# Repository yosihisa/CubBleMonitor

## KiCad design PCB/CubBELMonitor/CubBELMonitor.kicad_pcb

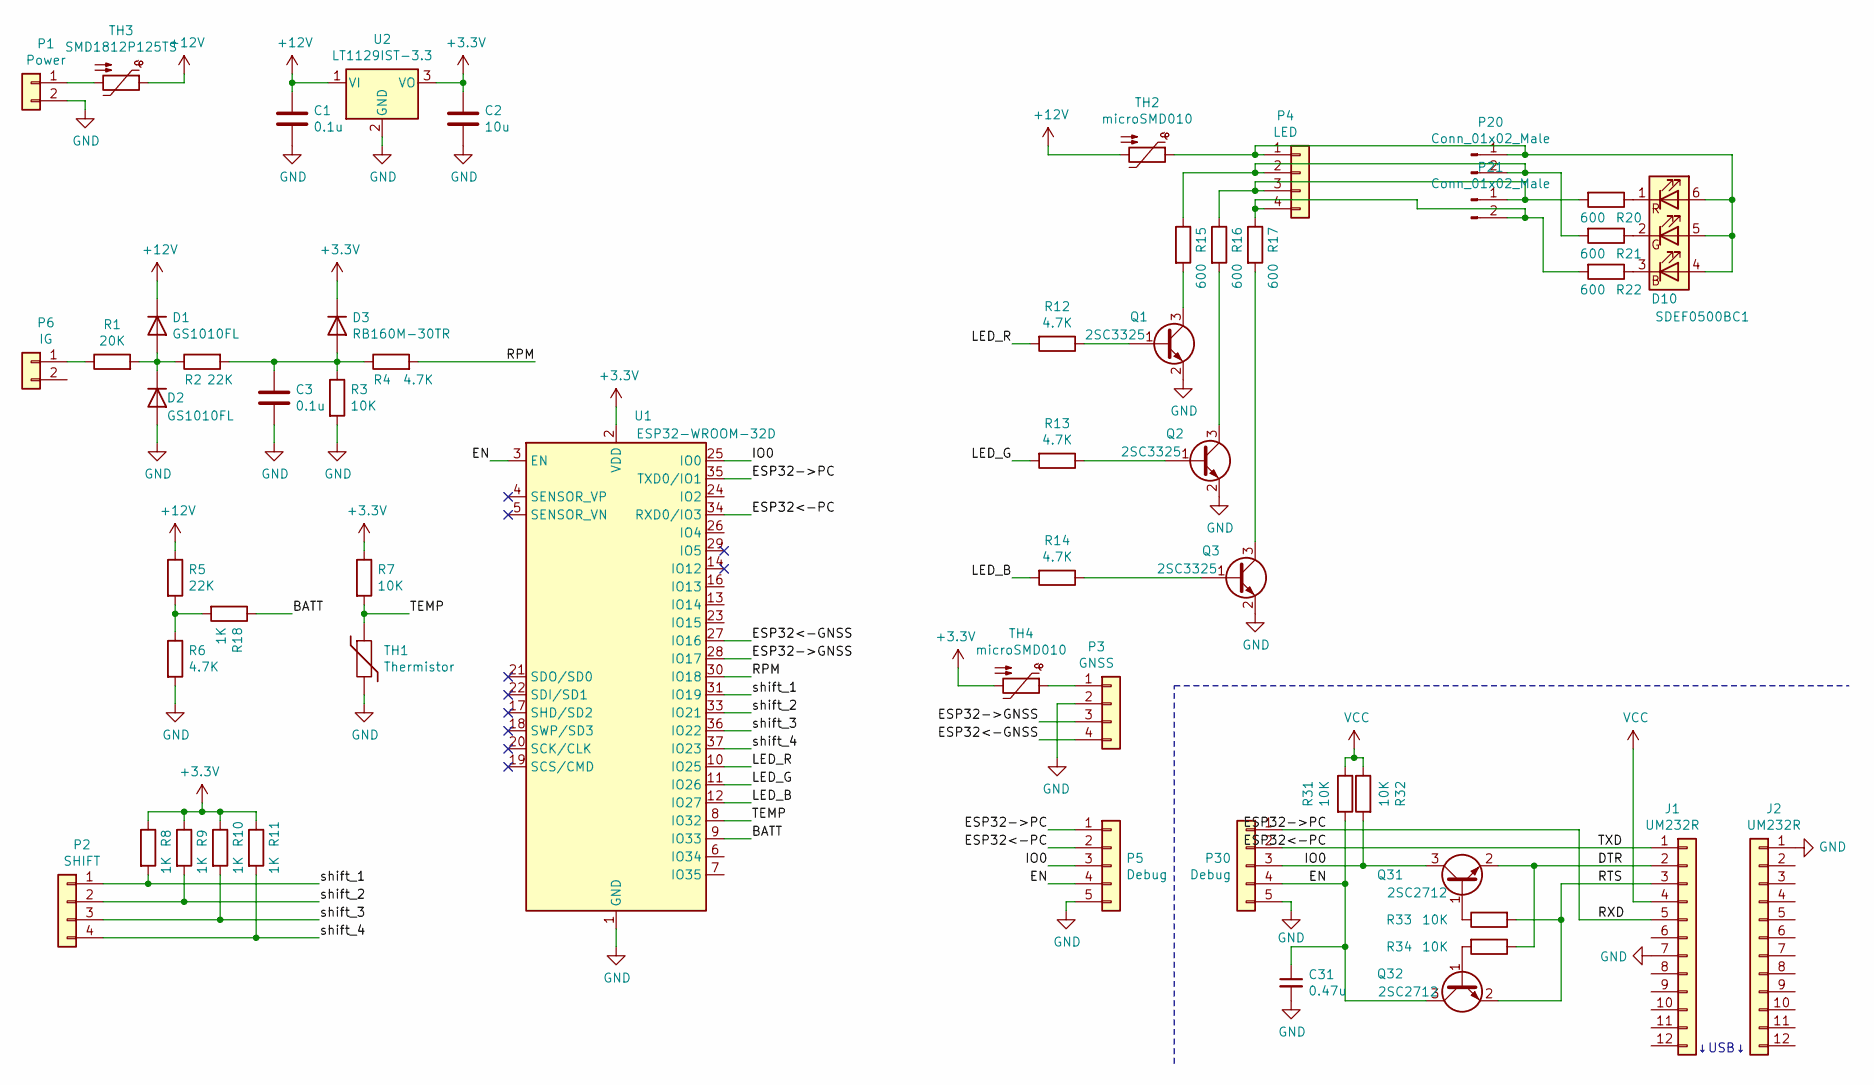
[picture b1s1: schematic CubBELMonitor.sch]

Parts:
C1, C3: 0.1u; C_0603_1608Metric_Pad1.05x0.95mm_HandSolder
C2: 10u; C_0805_2012Metric_Pad1.15x1.40mm_HandSolder
C31: 0.47u; C_0805_2012Metric_Pad1.15x1.40mm_HandSolder
D1, D2: GS1010FL; D_SOD-123
D3: RB160M-30TR; D_SOD-123
D10: SDEF0500BC1; LED_Avago_PLCC6_3x2.8mm
J1, J2: UM232R; PinHeader_1x12_P2.54mm_Vertical
P1: Power; JST_XH_S2B-XH-A_1x02_P2.50mm_Horizontal
P2: SHIFT; JST_XH_S4B-XH-A_1x04_P2.50mm_Horizontal
P3: GNSS; JST_XH_S4B-XH-A_1x04_P2.50mm_Horizontal
P4: LED; JST_XH_S4B-XH-A_1x04_P2.50mm_Horizontal
P5: Debug; PinSocket_1x05_P2.54mm_Vertical
P6: IG; JST_XH_B2B-XH-A_1x02_P2.50mm_Vertical
P20, P21: Conn_01x02_Male; 3mmLED_
P30: Debug; PinHeader_1x05_P2.54mm_Vertical
Q1, Q2, Q3: 2SC3325; SC-59
Q31, Q32: 2SC2712; SC-59
R1: 20K; R_0603_1608Metric_Pad1.05x0.95mm_HandSolder
R2, R5: 22K; R_0603_1608Metric_Pad1.05x0.95mm_HandSolder
R3, R7, R31, R32, R33, R34: 10K; R_0603_1608Metric_Pad1.05x0.95mm_HandSolder
R4, R6, R12, R13, R14: 4.7K; R_0603_1608Metric_Pad1.05x0.95mm_HandSolder
R8, R9, R10, R11, R18: 1K; R_0603_1608Metric_Pad1.05x0.95mm_HandSolder
R15, R16, R17, R20, R21, R22: 600; R_0603_1608Metric_Pad1.05x0.95mm_HandSolder
TH1: Thermistor; R_0603_1608Metric_Pad1.05x0.95mm_HandSolder
TH2, TH4: microSMD010; R_1210_3225Metric_Pad1.42x2.65mm_HandSolder
TH3: SMD1812P125TS; R_1812_4532Metric_Pad1.30x3.40mm_HandSolder
U1: ESP32-WROOM-32D; ESP32-WROOM-32
U2: LT1129IST-3.3; SOT-223-3_TabPin2

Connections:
+3V3: C2.1, D3.1 (K), R7.1, R8.1, R9.1, R10.1, R11.1, TH4.2, U1.2 (VDD), U2.3 (VO)
+12V: C1.1, D1.1 (K), R5.1, TH2.2, TH3.1, U2.1 (VI)
/BATT: R18.1, U1.9 (IO33)
/DTR: J1.2, Q31.2 (E), R34.1
/EN: C31.1, P5.4, P30.4, Q32.3 (C), R31.2, U1.3 (EN)
/ESP32->GNSS: P3.3, U1.28 (IO17)
/ESP32->PC: J1.5, P5.1, P30.1, U1.35 (TXD0/IO1)
/ESP32<-GNSS: P3.4, U1.27 (IO16)
/ESP32<-PC: J1.1, P5.2, P30.2, U1.34 (RXD0/IO3)
/IO0: P5.3, P30.3, Q31.3 (C), R32.2, U1.25 (IO0)
/LED_B: R14.2, U1.12 (IO27)
/LED_G: R13.2, U1.11 (IO26)
/LED_R: R12.2, U1.10 (IO25)
/RPM: R4.2, U1.30 (IO18)
/RTS: J1.3, Q32.2 (E), R33.2
/TEMP: R7.2, TH1.1, U1.8 (IO32)
/shift_1: P2.1, R8.2, U1.31 (IO19)
/shift_2: P2.2, R9.2, U1.33 (IO21)
/shift_3: P2.3, R10.2, U1.36 (IO22)
/shift_4: P2.4, R11.2, U1.37 (IO23)
GND: C1.2, C2.2, C3.2, C31.2, D2.2 (A), J1.7, J2.1, P1.2, P3.2, P5.5, P30.5, Q1.2 (E), Q2.2 (E), Q3.2 (E), R3.2, R6.2, TH1.2, U1.1 (GND), U1.15 (GND), U1.38 (GND), U1.39 (GND), U2.2 (GND)
unnamed: C3.1, D3.2 (A), R2.2, R3.1, R4.1
unnamed: D1.2 (A), D2.1 (K), R1.2, R2.1
unnamed: D10.1 (RK), R20.1
unnamed: D10.2 (GK), R21.1
unnamed: D10.3 (BK), R22.1
unnamed: D10.4 (BA), D10.5 (GA), D10.6 (RA), P4.1, P20.1, TH2.1
unnamed: P1.1, TH3.2
unnamed: P3.1, TH4.1
unnamed: P6.1, R1.1
unnamed: P4.2, P20.2, R15.1, R21.2
unnamed: P4.3, P21.1, R16.1, R20.2
unnamed: P4.4, P21.2, R17.1, R22.2
unnamed: Q1.1 (B), R12.1
unnamed: Q1.3 (C), R15.2
unnamed: Q2.1 (B), R13.1
unnamed: Q2.3 (C), R16.2
unnamed: Q3.1 (B), R14.1
unnamed: Q3.3 (C), R17.2
unnamed: Q31.1 (B), R33.1
unnamed: Q32.1 (B), R34.2
unnamed: R5.2, R6.1, R18.2
VCC: J1.4, R31.1, R32.1

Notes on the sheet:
↓USB↓

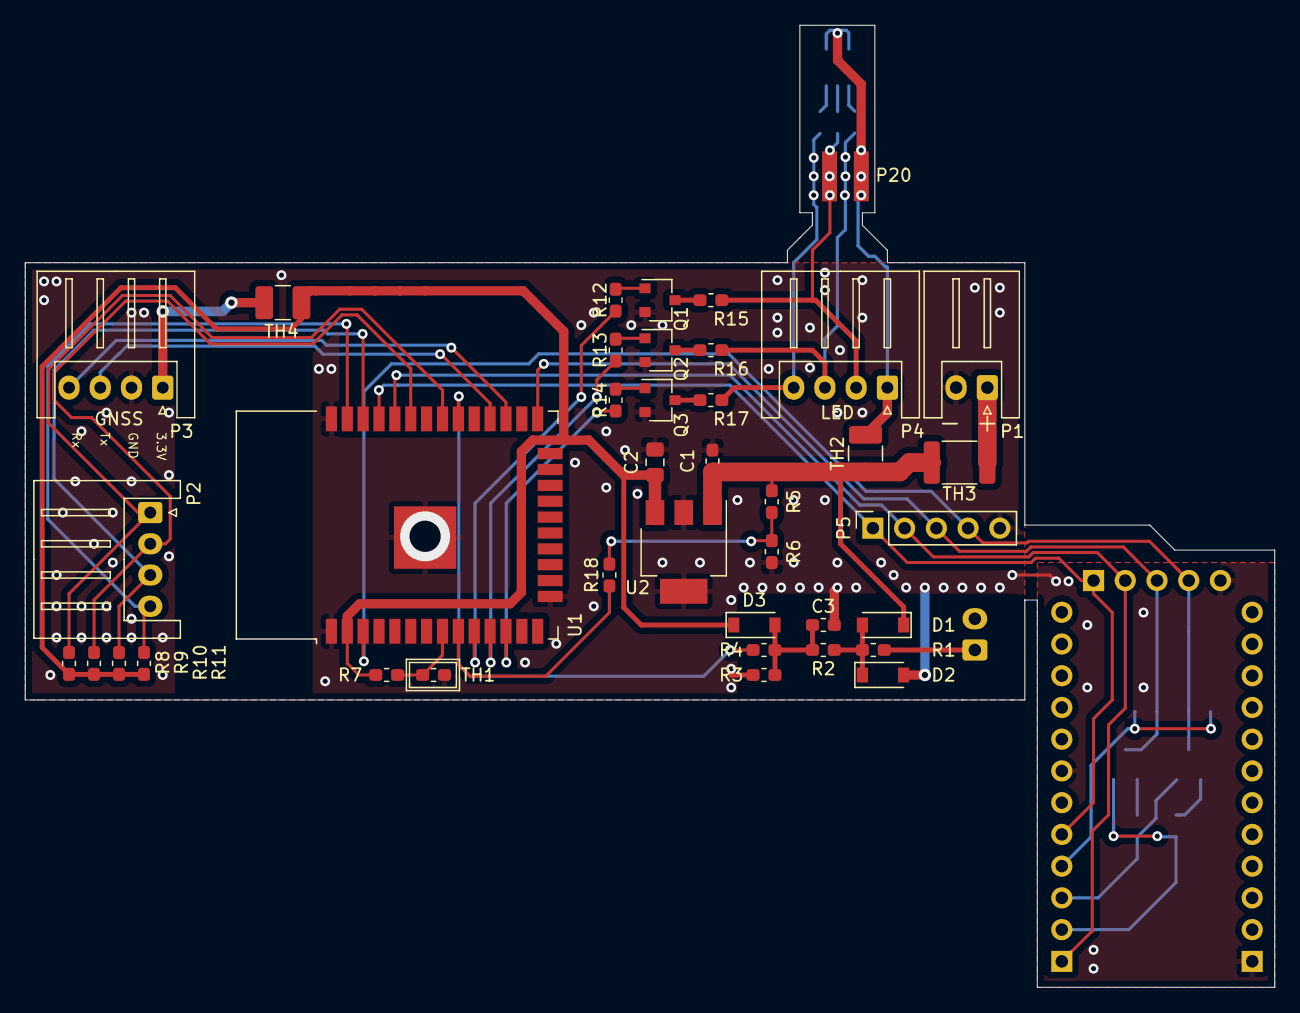
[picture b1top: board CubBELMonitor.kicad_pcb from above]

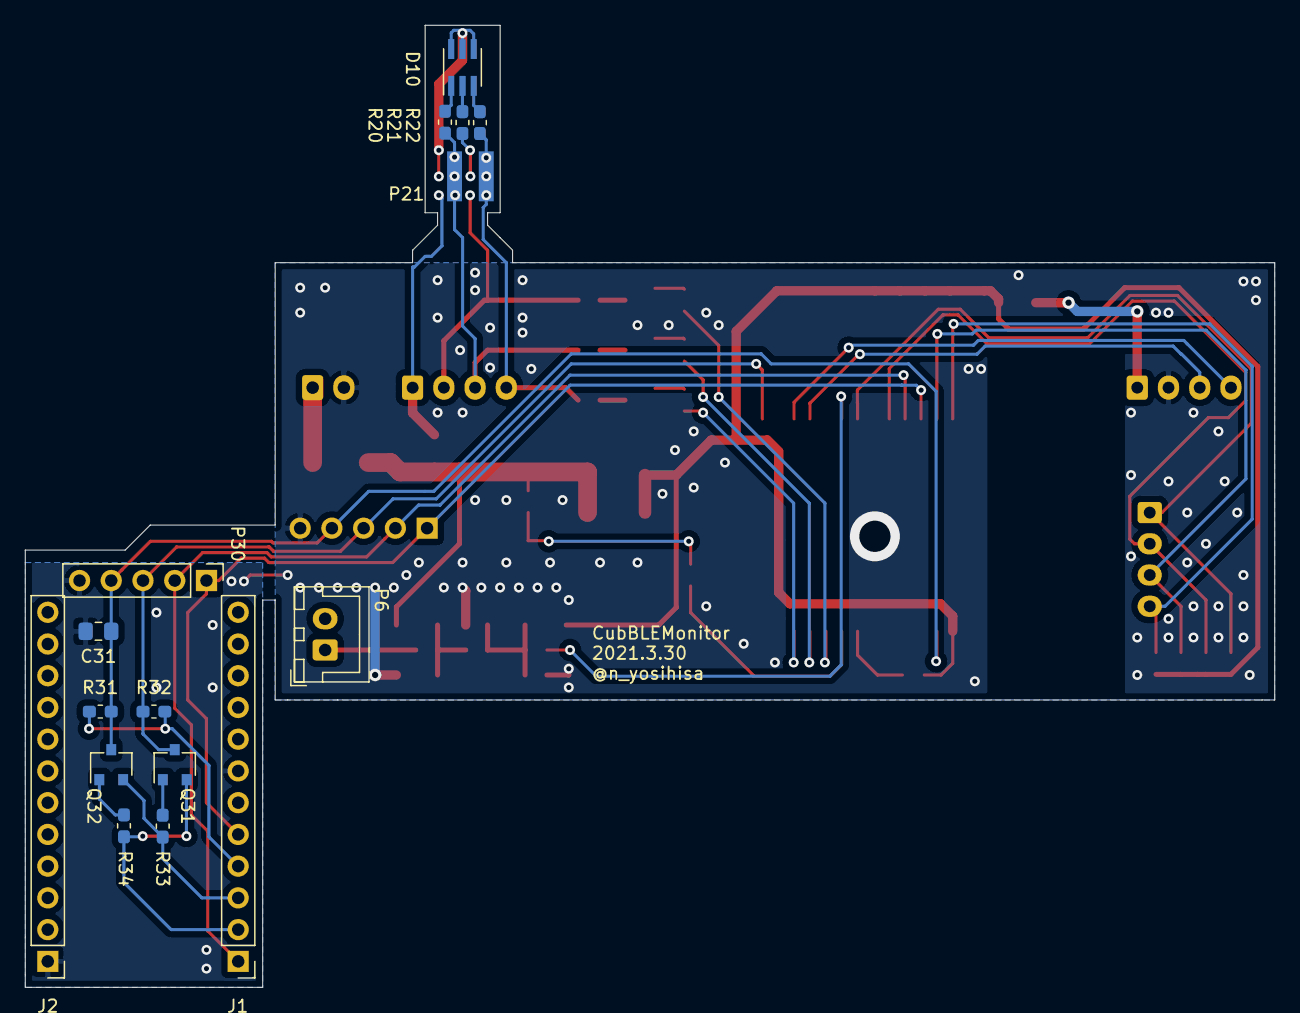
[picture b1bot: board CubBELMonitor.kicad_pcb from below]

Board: 2 copper layers, 100.0 x 77.0 mm, 55 parts (16 on the bottom side), 43 nets.

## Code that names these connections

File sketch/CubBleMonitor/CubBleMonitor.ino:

#include <WiFi.h>
#include <ESPmDNS.h>
#include <WiFiUdp.h>
#include <ArduinoOTA.h>

#include <BLEDevice.h>
#include <BLEUtils.h>
#include <BLEServer.h>
#include <BLE2902.h>

//OTAアップデート用のWiFiアクセスポイントの設定
const char *ssid = "ESP-UPDATE";
const char *password = "ESP32ESP32";

//BLEのUUID
#define SERVICE_UUID "90af54ef-d367-41ec-ac04-b3f9f42cdcb2"
#define CHARACTERISTIC_UUID "a018d2c9-5838-4196-bd97-d00547de2c57"

//点火パルス
#define RPM_PIN 18
#define SMOOTHING 3

//LED
#define LED_R_PIN 25
#define LED_G_PIN 26
#define LED_B_PIN 27

#define LEDC_TIMER_BIT 8
#define LEDC_BASE_FREQ 12800
#define LED_R_CHANNEL 0
#define LED_G_CHANNEL 1
#define LED_B_CHANNEL 2

//シフトインジケータ
#define SHIFT_1_PIN 19
#define SHIFT_2_PIN 21
#define SHIFT_3_PIN 22
#define SHIFT_4_PIN 23

//バッテリー電圧
#define BATT_PIN 33

//基板温度
#define TEMP_PIN 32

//GNSS
HardwareSerial Serial_GNSS(2); // UART2 (RX=16, TX=17)

//BLE
BLECharacteristic *pCharacteristic;
bool deviceConnected = false;

//Timer
#define COUNTER_PERIOD 30* 1000 * 100
#define COUNTER_DIVIDE 800
uint64_t timeCounter;
uint64_t ignition_cycle[SMOOTHING];
uint8_t ignition_num;

uint16_t  rpm   = 0;    //0～1023(10bit) 0～65536
uint8_t   shift = 0; //0～7(3bit) 0～255
uint8_t   temp  = 0; //-10～245(8bit)
uint8_t   batt  = 0; //0～255(8bit)
uint16_t  speed = 0; //0～255(8bit)
uint8_t   mode  = 0; //N A D E

bool ota_mode = false;
int cnt;

#include "init.h"
#include "function.h"


void IRAM_ATTR rpm_pulse() {
  uint64_t now_time = esp_timer_get_time();
  uint64_t dt = now_time - timeCounter;
  if(dt > 12000){
    ignition_cycle[ignition_num] = dt;
    ignition_num = (ignition_num + 1) % SMOOTHING;
    timeCounter = now_time;
  }
  return;
}

void setup() {
  Serial.begin(115200);
  Serial.println("Cub Avio");

  PIN_setup();
  led_rgb(255, 255, 255);
  GNSS_setup();

  //3速で起動したらOTAを有効にする
  if (digitalRead(SHIFT_3_PIN) == LOW){
    led_rgb(255, 50, 50);
    OTA_setup();
    ota_mode = true;
    for (int i = 0; i<5; i++) {
      led_rgb(0, 255, 0);
      delay(200);
      led_rgb(0, 0, 0);
      delay(200);
    }
  }
  
  //BLE開始
  BLE_setup();

  //点火パルスの割り込み開始
  ignition_num = 0;
  for(int i=0;i< SMOOTHING;i++){
    ignition_cycle[i] = 0;
  }

  if (ota_mode != true){
    attachInterrupt(RPM_PIN, rpm_pulse, FALLING);
  }
  led_rgb(0, 0, 0);
}

void loop() {

  if ( ota_mode == true ) ArduinoOTA.handle();

  uint64_t sum_cycle = 0;
  for (int i = 0; i < SMOOTHING; i++) {
    sum_cycle += ignition_cycle[i];
  }
  if (sum_cycle!=0){
    rpm = (uint32_t)1000 * 1000 * 60 * 2 * SMOOTHING / sum_cycle;
  }else{
    rpm = 0;
  }
  shift = read_shift();
  batt = (uint32_t) analogRead(BATT_PIN) * 33 * (1000) / 165 / 4096;
  temp = (float)-0.0259 * analogRead(TEMP_PIN) + 78.263 + 20;

  
  //GNSS取得
  String cmds[15] = {"\0"};
  String data = Serial_GNSS.readStringUntil('\n'); //1行読み込み
  int index = split(data, ',', cmds);              // , で分割
  if(index >=10){
    speed = cmds[7].toFloat() * 10;                //速度を取り出し
    mode  = cmds[9].charAt(0);                     //取得状況を取り出し
  }

  //BLE送信
  if (deviceConnected) {
    uint8_t BLE_tx_buff[8] = {0};

    BLE_tx_buff[0] = (uint8_t)(rpm >> 8);
    BLE_tx_buff[1] = (uint8_t)(rpm >> 0);
    BLE_tx_buff[2] = shift;
    BLE_tx_buff[3] = temp;
    BLE_tx_buff[4] = batt;
    BLE_tx_buff[5] = (uint8_t)(speed >> 8);
    BLE_tx_buff[6] = (uint8_t)(speed >> 0);
    BLE_tx_buff[7] = mode;

    pCharacteristic->setValue(BLE_tx_buff, 8);
    pCharacteristic->notify();

  }

  //シフトインジケータ表示
  indicate_LED();

  char str[50];
  sprintf(str, "%04d ,%d ,%3d ,%3d ,%3d [%d] ,%ld", rpm, shift, temp - 20, batt, speed, mode, ignition_cycle[0]);
  Serial.println(str);
}

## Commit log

2021-02-06 Add html
2021-02-06 Rename doc
2021-02-06 rename docs
2021-02-06 Add BLE.js
2021-02-07 GNSS追加
2021-02-07 UI作成
2021-02-07 UI更新
2021-02-07 時計追加 UI調整
2021-02-09 lang="ja"
2021-02-09 時計修正
2021-02-12 回路図作成
2021-02-13 速度色変更
2021-02-14 内蔵温度センサ有効化
2021-03-26 Add simulation
2021-03-26 ボード追加
2021-03-30 基板更新
2021-03-30 Gerber追加
2021-03-30 自動再接続追加
2021-04-06 タコメータの分解能向上
2021-04-06 GNSS以外の全機能を追加
2021-04-07 ノイズ対策追加
2021-04-09 旧ファイル移動
2021-04-09 メーターレイアウト更新
2022-08-13 viewportの変更
2022-08-13 倍率固定
2022-08-13 PWAに仮対応
2022-08-13 レイアウト変更
